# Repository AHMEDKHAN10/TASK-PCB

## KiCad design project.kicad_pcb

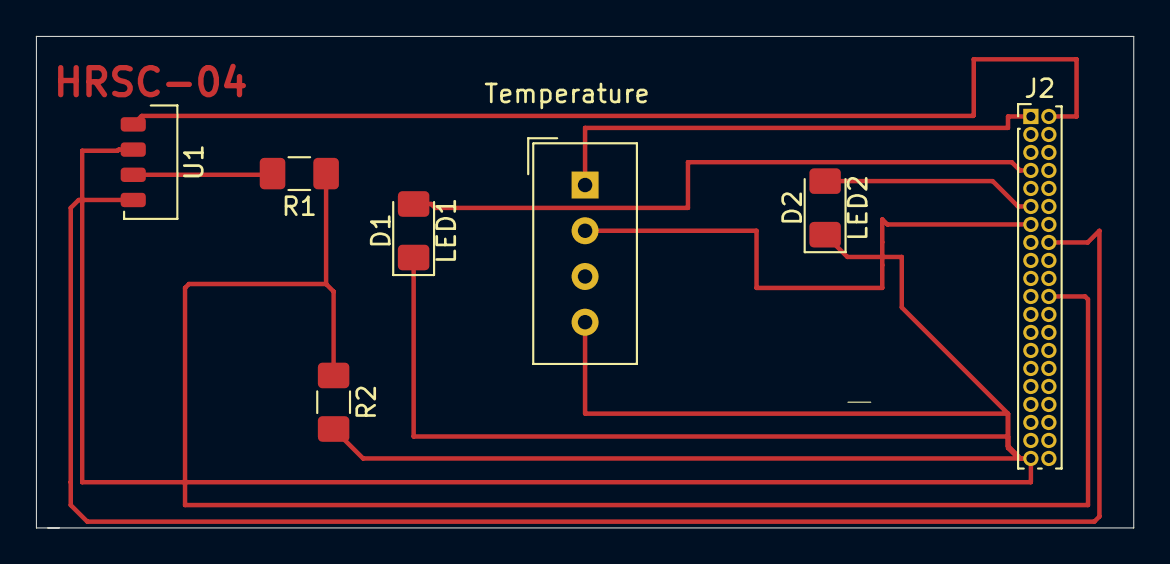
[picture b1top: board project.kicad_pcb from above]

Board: 2 copper layers, 61.0 x 27.3 mm, 7 parts (0 on the bottom side), 9 nets.

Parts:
D1: LED1; LED_1206_3216Metric_Pad1.42x1.75mm_HandSolder
D2: LED2; LED_1206_3216Metric_Pad1.42x1.75mm_HandSolder
J2: Conn_02x20_Odd_Even; PinHeader_2x20_P1.00mm_Vertical
R1: 1K; R_1206_3216Metric_Pad1.42x1.75mm_HandSolder
R2: 2K; R_1206_3216Metric_Pad1.42x1.75mm_HandSolder
Temperature: DHT11; Aosong_DHT11_5.5x12.0_P2.54mm
U1: HCSR-04; Kingbright_KRC011_Vertical

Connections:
unnamed: D1.1, D2.1, J2.39, R2.2, Temperature.4, U1.2
unnamed: D1.2, J2.7
unnamed: D2.2, J2.11
unnamed: J2.1, Temperature.1
unnamed: J2.2, U1.1
unnamed: J2.13, Temperature.2
unnamed: J2.16, U1.4
unnamed: J2.22, R1.1, R2.1
unnamed: R1.2, U1.3
